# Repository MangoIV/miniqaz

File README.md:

# miniqaz
sis is se minni kwarz

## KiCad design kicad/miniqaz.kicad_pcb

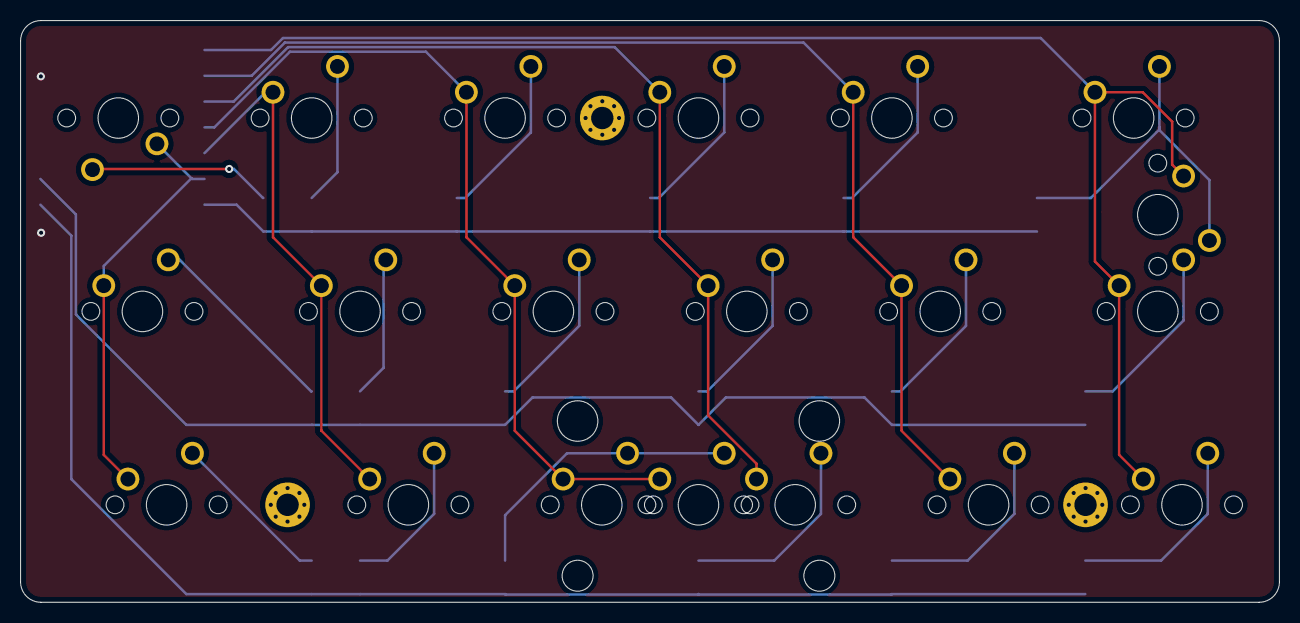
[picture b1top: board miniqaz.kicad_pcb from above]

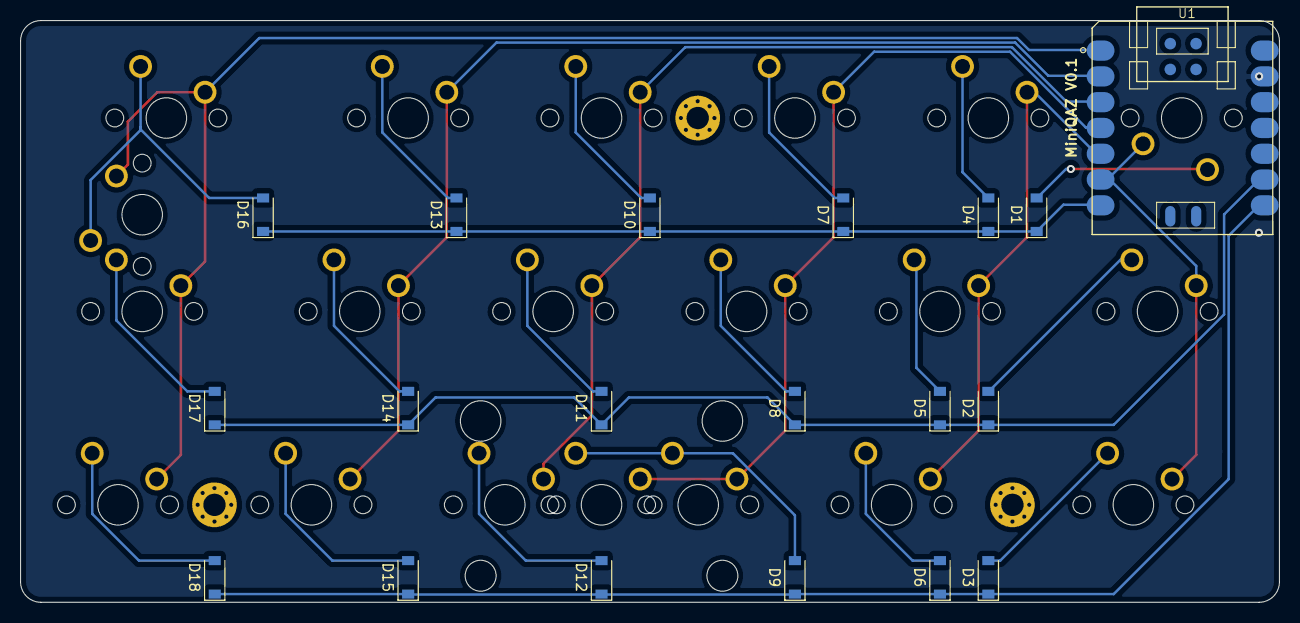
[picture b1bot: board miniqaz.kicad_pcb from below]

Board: 2 copper layers, 124.0 x 57.3 mm, 42 parts (19 on the bottom side), 27 nets.

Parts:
 : MountingHole_2.2mm_M2_Pad_Via
 #2,  #3: MountingHole_2.2mm_M2_Pad_Via
D1, D2, D3, D4, D5, D6, D7, D8, D9, D10, D11, D12, D13, D14, D15, D16, D17, D18: D_Small; D_SOD-123
MX1, MX4, MX5, MX6, MX7, MX8, MX9, MX10, MX11, MX12, MX13, MX14, MX15, MX18, MX20: MX-NoLED; MXOnly-1U-NoLED
MX2, MX17: MX-NoLED; MXOnly-1.25U-NoLED
MX3, MX16: MX-NoLED; MXOnly-1.5U-NoLED
MX19: MX-NoLED; MXOnly-2U-ReversedStabilizers-NoLED
U1: Seeeduino XIAO-MOUDLE14P-2.54-21X17.8MM

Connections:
unnamed: D1.2, MX1.2
unnamed: D2.2, MX2.2
unnamed: D3.2, MX3.2
unnamed: D4.2, MX4.2
unnamed: D5.2, MX5.2
unnamed: D6.2, MX6.2
unnamed: D7.2, MX7.2
unnamed: D8.2, MX8.2
unnamed: D10.2, MX10.2
unnamed: D11.2, MX11.2
unnamed: D12.2, MX12.2
unnamed: D13.2, MX13.2
unnamed: D14.2, MX14.2
unnamed: D15.2, MX15.2
unnamed: D17.2, MX17.2
unnamed: D18.2, MX18.2
col0: MX1.1, MX2.1, MX3.1, U1.6
col1: MX4.1, MX5.1, MX6.1, U1.5
col2: MX7.1, MX8.1, MX9.1, MX19.1, U1.4
col3: MX10.1, MX11.1, MX12.1, U1.3
col4: MX13.1, MX14.1, MX15.1, U1.2
col5: MX16.1, MX17.1, MX18.1, MX20.1, U1.1
erow: D16.2, MX16.2, MX20.2
row0: D1.1, D4.1, D7.1, D10.1, D13.1, D16.1, U1.7
row1: D2.1, D5.1, D8.1, D11.1, D14.1, D17.1, U1.9
row2: D3.1, D6.1, D9.1, D12.1, D15.1, D18.1, U1.8
srow: D9.2, MX9.2, MX19.2

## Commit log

2021-04-21 added seeeduino xiao symbol and footprint
2021-04-21 added miniqaz
2021-04-21 added gerbers
2021-04-21 removed accidentally generated files
2021-04-22 design updates
    - Added relative Path for MX-Switch lib
    - Modified Seeeduino Xiao footprint to move origin to the center
    - Centered Seeeduino Xia Footprint under the top-left key
2021-04-22 moved single via a few millimeters
